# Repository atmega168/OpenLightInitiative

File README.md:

OpenLightInitiative
===================

A collection of code and schematics for making custom/hackable lighting.

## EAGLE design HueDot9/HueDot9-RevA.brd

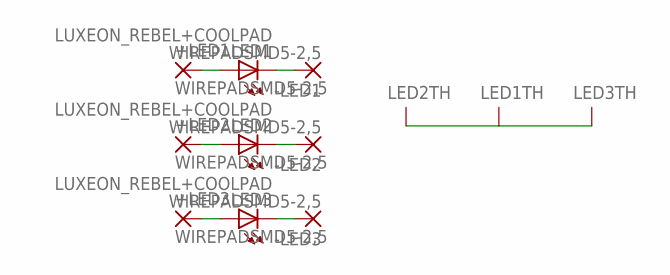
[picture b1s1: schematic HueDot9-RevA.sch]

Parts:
+LED1, +LED2, +LED3: WIREPADSMD5-2,5; 5-2,5
-LED1, -LED2, -LED3: WIREPADSMD5-2,5; 5-2,5
LED1, LED2, LED3: LUXEON_REBEL+COOLPAD

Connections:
AN1: +LED1.1, LED1.A, LED1.A@1 (A)
AN2: +LED2.1, LED2.A, LED2.A@1 (A)
AN3: +LED3.1, LED3.A, LED3.A@1 (A)
CA1: -LED1.1, LED1.C, LED1.C@1 (C)
CA2: -LED2.1, LED2.C, LED2.C@1 (C)
CN3: -LED3.1, LED3.C, LED3.C@1 (C)
TH: LED1.TH, LED1.TH@1 (TH), LED1.TH@2 (TH), LED1.TH@3 (TH), LED1.TH@4 (TH), LED1.TH@5 (TH), LED1.TH@6 (TH), LED1.TH@7 (TH), LED1.TH@8 (TH), LED1.TH@9 (TH), LED1.TH@10 (TH), LED1.TH@11 (TH), LED1.TH@12 (TH), LED1.TH@13 (TH), LED1.TH@14 (TH), LED1.TH@15 (TH), LED1.TH@16 (TH), LED1.TH@17 (TH), LED1.TH@18 (TH), LED1.TH@19 (TH), LED1.TH@20 (TH), LED1.TH@21 (TH), LED1.TH@22 (TH), LED1.TH@23 (TH), LED1.TH@24 (TH), LED1.TH@25 (TH), LED1.TH@26 (TH), LED1.TH@27 (TH), LED1.TH@28 (TH), LED1.TH@29 (TH), LED1.TH@30 (TH), LED1.TH@31 (TH), LED1.TH@32 (TH), LED1.TH@33 (TH), LED1.TH@34 (TH), LED1.TH@35 (TH), LED2.TH, LED2.TH@1 (TH), LED2.TH@2 (TH), LED2.TH@3 (TH), LED2.TH@4 (TH), LED2.TH@5 (TH), LED2.TH@6 (TH), LED2.TH@7 (TH), LED2.TH@8 (TH), LED2.TH@9 (TH), LED2.TH@10 (TH), LED2.TH@11 (TH), LED2.TH@12 (TH), LED2.TH@13 (TH), LED2.TH@14 (TH), LED2.TH@15 (TH), LED2.TH@16 (TH), LED2.TH@17 (TH), LED2.TH@18 (TH), LED2.TH@19 (TH), LED2.TH@20 (TH), LED2.TH@21 (TH), LED2.TH@22 (TH), LED2.TH@23 (TH), LED2.TH@24 (TH), LED2.TH@25 (TH), LED2.TH@26 (TH), LED2.TH@27 (TH), LED2.TH@28 (TH), LED2.TH@29 (TH), LED2.TH@30 (TH), LED2.TH@31 (TH), LED2.TH@32 (TH), LED2.TH@33 (TH), LED2.TH@34 (TH), LED2.TH@35 (TH), LED3.TH, LED3.TH@1 (TH), LED3.TH@2 (TH), LED3.TH@3 (TH), LED3.TH@4 (TH), LED3.TH@5 (TH), LED3.TH@6 (TH), LED3.TH@7 (TH), LED3.TH@8 (TH), LED3.TH@9 (TH), LED3.TH@10 (TH), LED3.TH@11 (TH), LED3.TH@12 (TH), LED3.TH@13 (TH), LED3.TH@14 (TH), LED3.TH@15 (TH), LED3.TH@16 (TH), LED3.TH@17 (TH), LED3.TH@18 (TH), LED3.TH@19 (TH), LED3.TH@20 (TH), LED3.TH@21 (TH), LED3.TH@22 (TH), LED3.TH@23 (TH), LED3.TH@24 (TH), LED3.TH@25 (TH), LED3.TH@26 (TH), LED3.TH@27 (TH), LED3.TH@28 (TH), LED3.TH@29 (TH), LED3.TH@30 (TH), LED3.TH@31 (TH), LED3.TH@32 (TH), LED3.TH@33 (TH), LED3.TH@34 (TH), LED3.TH@35 (TH)

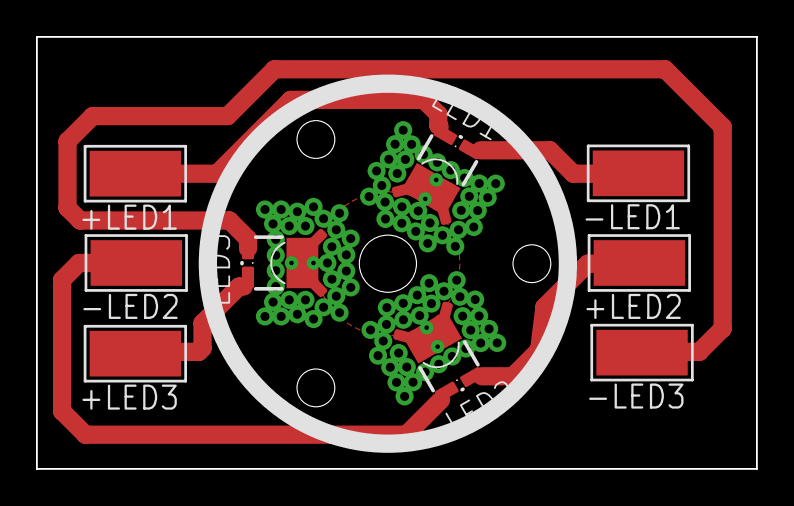
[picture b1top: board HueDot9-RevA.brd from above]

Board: 2 copper layers, 40.0 x 24.0 mm, 9 parts (0 on the bottom side), 7 nets.

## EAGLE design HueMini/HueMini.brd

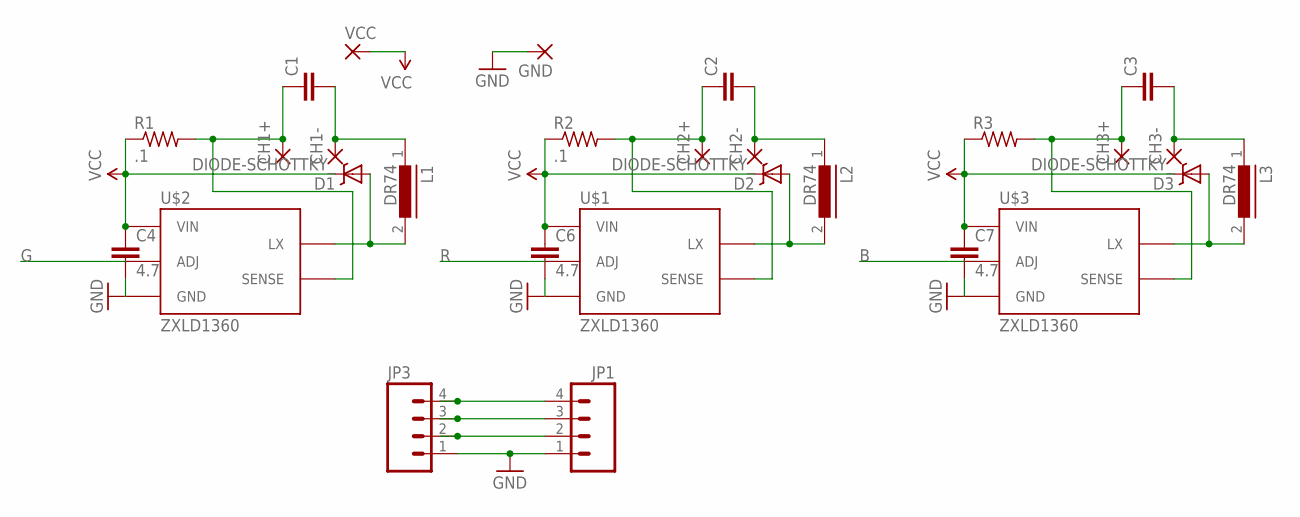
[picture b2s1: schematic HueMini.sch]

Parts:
C1, C2, C3: CAP0603-CAP; 0603-CAP
C4, C6, C7: 4.7; C1206
CH1+, CH1-, CH2+, CH2-, CH3+, CH3-: SMD5; SMD2,54-5,08
D1, D2, D3: DIODE-SCHOTTKY_; SMA-DIODE
GND: SMD5; SMD2,54-5,08
JP1, JP3: M04PTH; 1X04
L1, L2, L3: DR74
R1, R2: .1; R0603
R3: R-US_R0603; R0603
U$1, U$2, U$3: ZXLD1360; SOT23-5
VCC: SMD5; SMD2,54-5,08

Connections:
B: JP1.2, JP3.2, U$3.3 (ADJ)
G: JP1.4, JP3.4, U$2.3 (ADJ)
GND: C4.2, C6.2, C7.2, GND.1, JP1.1, JP3.1, U$1.2 (GND), U$2.2 (GND), U$3.2 (GND)
unnamed: C2.2, CH2-.1, L2.1
unnamed: C2.1, CH2+.1, R2.2, U$1.4 (SENSE)
unnamed: C1.2, CH1-.1, L1.1
unnamed: C1.1, CH1+.1, R1.2, U$2.4 (SENSE)
unnamed: D2.A, L2.2, U$1.1 (LX)
unnamed: C3.2, CH3-.1, L3.1
unnamed: C3.1, CH3+.1, R3.2, U$3.4 (SENSE)
unnamed: D3.A, L3.2, U$3.1 (LX)
unnamed: D1.A, L1.2, U$2.1 (LX)
R: JP1.3, JP3.3, U$1.3 (ADJ)
VCC: C4.1, C6.1, C7.1, D1.C, D2.C, D3.C, R1.1, R2.1, R3.1, U$1.5 (VIN), U$2.5 (VIN), U$3.5 (VIN), VCC.1

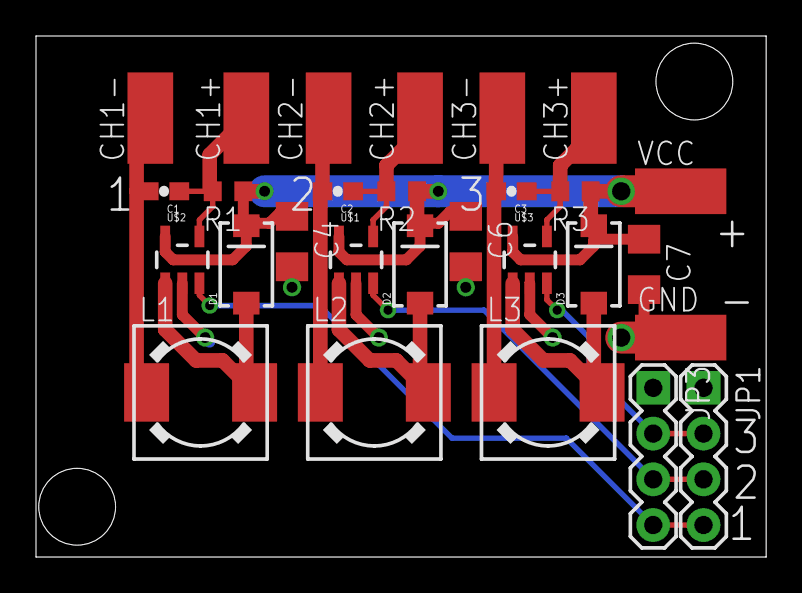
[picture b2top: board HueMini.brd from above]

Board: 2 copper layers, 40.6 x 28.9 mm, 28 parts (0 on the bottom side), 14 nets.

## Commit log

2014-01-23 Added the HueMini. HueMini is a 1Amp Constant Current Driver for LEDs based on the ZXLD1360: http://www.diodes.com/datasheets/ZXLD1360.pdf It is a buck converter and it can take up to 30 Volts. This 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
2014-01-23 Added an image of the HueMini layout for previewing
2014-01-25 Added the HueDot9 Rev A, a board designed to work with the REBEL LEDs. Supports standard 10mm Lenses like the Carclo Technical Plastics 10511 http://www.carclo-optics.com/sites/default/files/images/o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
2014-01-25 Updated Layout Photo
